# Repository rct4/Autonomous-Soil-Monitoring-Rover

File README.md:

# Autonomous-Soil-Monitoring-Rover

The autonomous soil monitoring rover is a project that aims to assist commercial farmers and personal gardeners by introducing an automated solution to monitoring soil data.

## Software
Motion plan is currently a naive solution, polling each sensor for feedback. A FreeRTOS solution is currently being developed to schedule sensor data collection and motor output.

## PCB

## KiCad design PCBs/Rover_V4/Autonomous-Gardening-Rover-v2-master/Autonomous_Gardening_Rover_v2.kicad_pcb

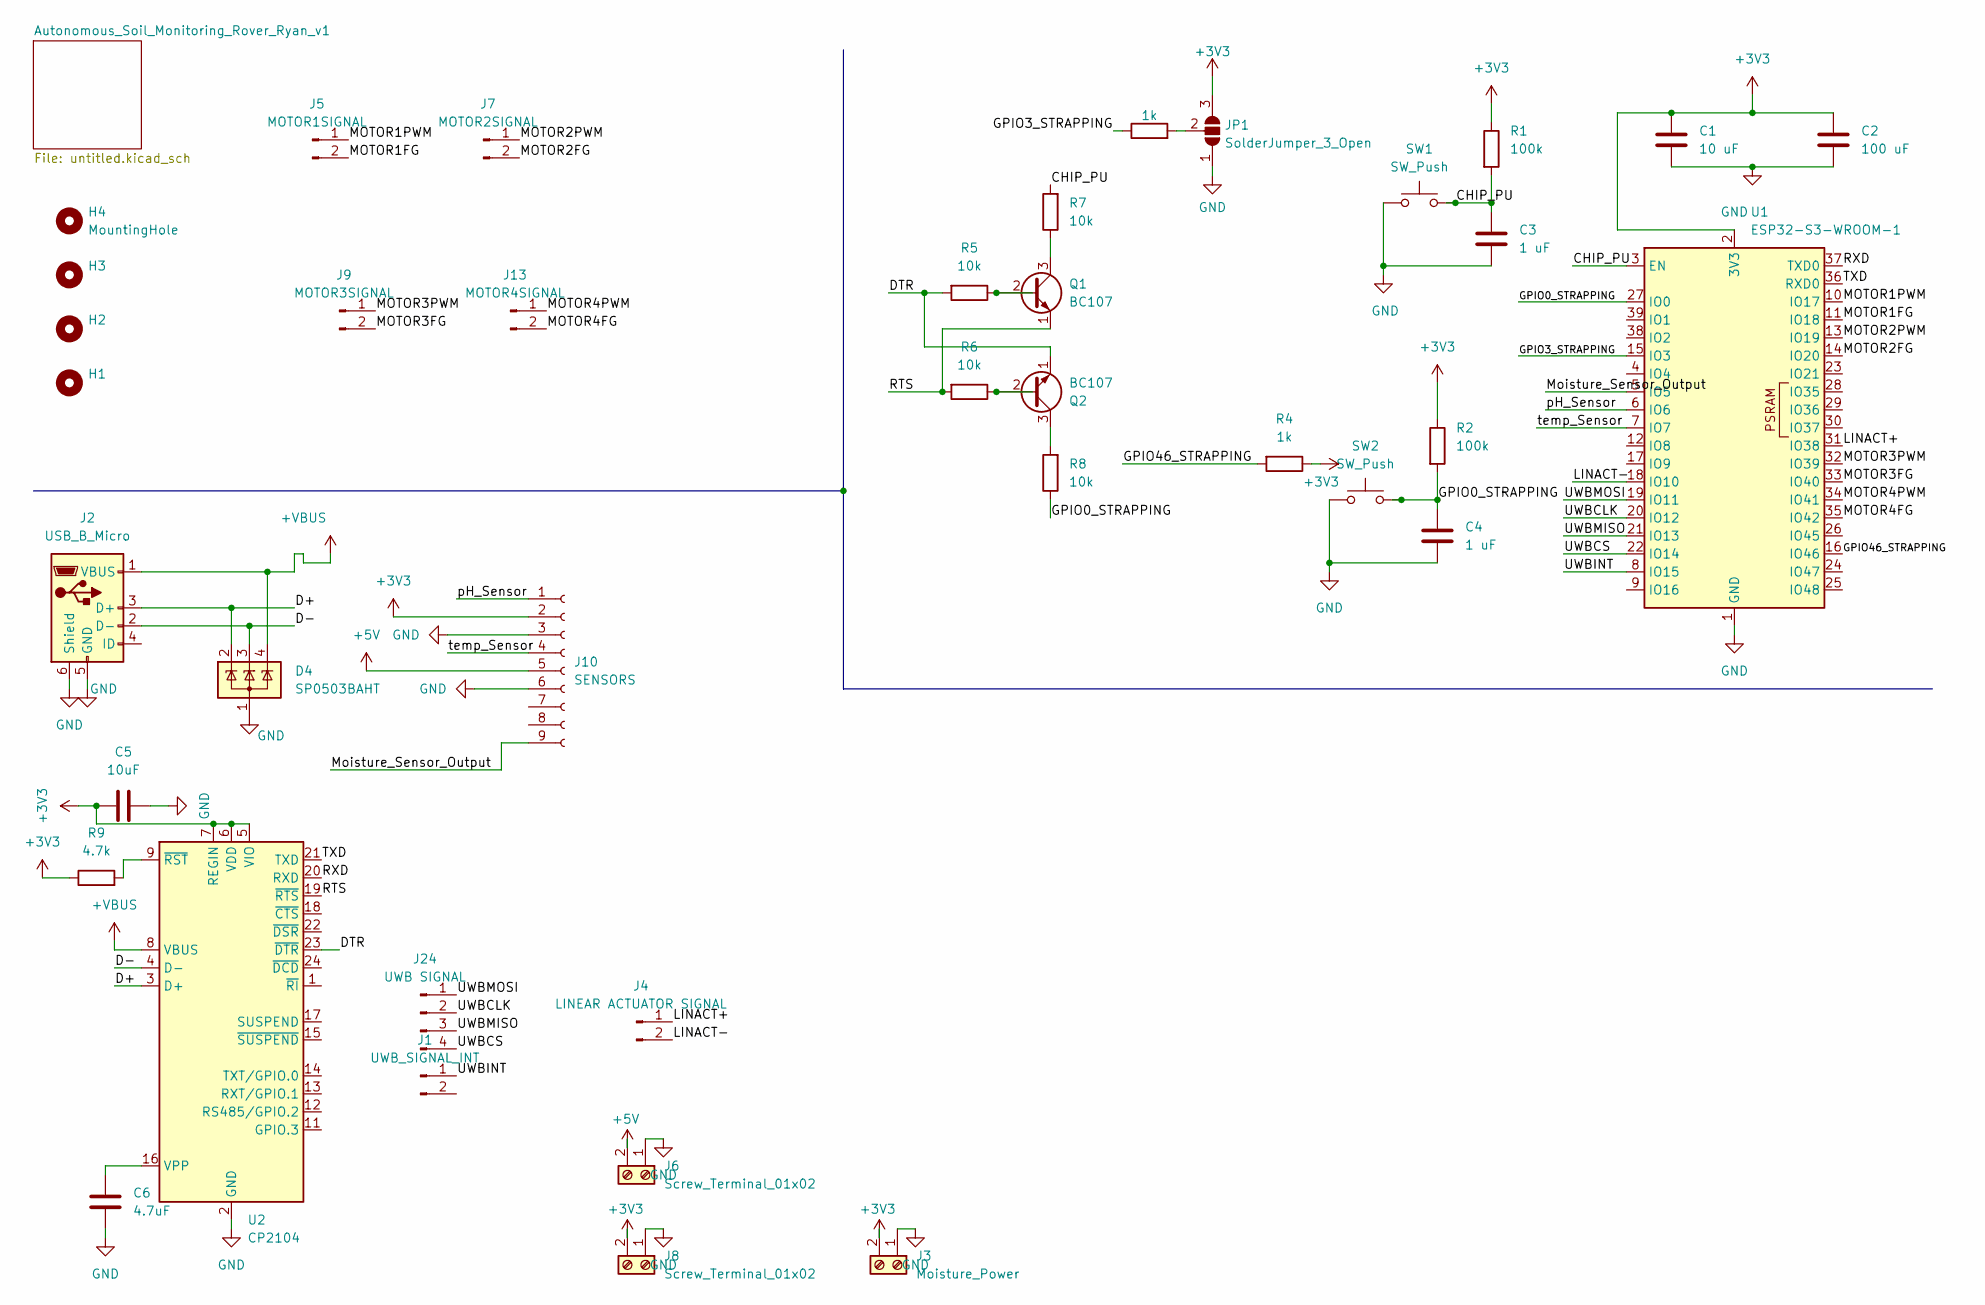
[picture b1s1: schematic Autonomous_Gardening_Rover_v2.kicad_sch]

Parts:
C1: 10 uF; C_0805_2012Metric_Pad1.18x1.45mm_HandSolder
C2: 100 uF; C_0805_2012Metric_Pad1.18x1.45mm_HandSolder
C3, C4: 1 uF; C_0805_2012Metric_Pad1.18x1.45mm_HandSolder
C5: 10uF; C_0805_2012Metric_Pad1.18x1.45mm_HandSolder
C6: 4.7uF; C_0805_2012Metric_Pad1.18x1.45mm_HandSolder
D4: SP0503BAHT; SOT-143
H1, H2, H3, H4: MountingHole; MountingHole_3.2mm_M3
J1: UWB_SIGNAL_INT; TerminalBlock_Phoenix_MKDS-1,5-2-5.08_1x02_P5.08mm_Horizont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
J2: USB_B_Micro; USB_Micro-B_Molex_47346-0001
J3: Moisture_Power; TerminalBlock_Phoenix_MKDS-1,5-2-5.08_1x02_P5.08mm_Horizont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
J4: LINEAR ACTUATOR SIGNAL; TerminalBlock_Phoenix_MKDS-1,5-2-5.08_1x02_P5.08mm_Horizont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
J5: MOTOR1SIGNAL; TerminalBlock_Phoenix_MKDS-1,5-2-5.08_1x02_P5.08mm_Horizont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
J6, J8: Screw_Terminal_01x02; TerminalBlock_Phoenix_MKDS-1,5-2-5.08_1x02_P5.08mm_Horizont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
J7: MOTOR2SIGNAL; TerminalBlock_Phoenix_MKDS-1,5-2-5.08_1x02_P5.08mm_Horizont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
J9: MOTOR3SIGNAL; TerminalBlock_Phoenix_MKDS-1,5-2-5.08_1x02_P5.08mm_Horizont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
J10: SENSORS; PinHeader_1x09_P2.54mm_Vertical
J13: MOTOR4SIGNAL; TerminalBlock_Phoenix_MKDS-1,5-2-5.08_1x02_P5.08mm_Horizont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
J24: UWB SIGNAL; TerminalBlock_Phoenix_MKDS-1,5-4-5.08_1x04_P5.08mm_Horizont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
JP1: SolderJumper_3_Open; SolderJumper-3_P2.0mm_Open_TrianglePad1.0x1.5mm
Q1, Q2: BC107; TO-18-3
R1, R2: 100k; R_0805_2012Metric_Pad1.20x1.40mm_HandSolder
R3: 1k; R_0805_2012Metric
R4: 1k; R_0805_2012Metric_Pad1.20x1.40mm_HandSolder
R5, R6, R7, R8: 10k; R_0805_2012Metric_Pad1.20x1.40mm_HandSolder
R9: 4.7k; R_0805_2012Metric_Pad1.20x1.40mm_HandSolder
SW1, SW2: SW_Push; SW_PUSH_6mm_H5mm
U1: ESP32-S3-WROOM-1; ESP32-S3-WROOM-1_EXP
U2: CP2104; QFN-24-1EP_4x4mm_P0.5mm_EP2.6x2.6mm

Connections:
+3V3: C1.1, C2.1, C5.1, J3.2, J8.2, J10.2, JP1.3 (B), R1.1, R2.1, R4.1, R9.1, U1.2 (3V3), U2.5 (VIO), U2.6 (VDD), U2.7 (REGIN)
+5V: J6.2, J10.5
+VBUS: D4.4 (K), J2.1 (VBUS), U2.8 (VBUS)
/CHIP_PU: C3.1, R1.2, R7.2, SW1.2, U1.3 (EN)
/D+: D4.2 (K), J2.3 (D+), U2.3 (D+)
/D-: D4.3 (K), J2.2 (D-), U2.4 (D-)
/DTR: Q2.1 (E), R5.2, U2.23 (~DTR)
/GPIO0_STRAPPING: C4.1, R2.2, R8.1, SW2.2, U1.27 (IO0)
/GPIO3_STRAPPING: R3.1, U1.15 (IO3)
/GPIO46_STRAPPING: R4.2, U1.16 (IO46)
/LINACT+: J4.1, U1.31 (IO38)
/LINACT-: J4.2, U1.18 (IO10)
/MOTOR1FG: J5.2, U1.11 (IO18)
/MOTOR1PWM: J5.1, U1.10 (IO17)
/MOTOR2FG: J7.2, U1.14 (IO20)
/MOTOR2PWM: J7.1, U1.13 (IO19)
/MOTOR3FG: J9.2, U1.33 (IO40)
/MOTOR3PWM: J9.1, U1.32 (IO39)
/MOTOR4FG: J13.2, U1.35 (IO42)
/MOTOR4PWM: J13.1, U1.34 (IO41)
/Moisture_Sensor_Output: J10.9, U1.5 (IO5)
/RTS: Q1.1 (E), R6.2, U2.19 (~RTS)
/RXD: U1.37 (TXD0), U2.20 (RXD)
/TXD: U1.36 (RXD0), U2.21 (TXD)
/UWBCLK: J24.2, U1.20 (IO12)
/UWBCS: J24.4, U1.22 (IO14)
/UWBINT: J1.1, U1.8 (IO15)
/UWBMISO: J24.3, U1.21 (IO13)
/UWBMOSI: J24.1, U1.19 (IO11)
/pH_Sensor: J10.1, U1.6 (IO6)
/temp_Sensor: J10.4, U1.7 (IO7)
GND: C1.2, C2.2, C3.2, C4.2, C5.2, C6.2, D4.1 (A), J2.5 (GND), J2.6 (Shield), J3.1, J6.1, J8.1, J10.3, J10.6, JP1.1 (A), SW1.1, SW2.1, U1.1 (GND), U1.40 (GND), U1.41 (GND), U2.2 (GND), U2.25 (GND)
unnamed: JP1.2 (C), R3.2
unnamed: Q1.2 (B), R5.1
unnamed: Q1.3 (C), R7.1
unnamed: Q2.2 (B), R6.1
unnamed: Q2.3 (C), R8.2
unnamed: C6.1, U2.16 (VPP)
unnamed: R9.2, U2.9 (~RST)

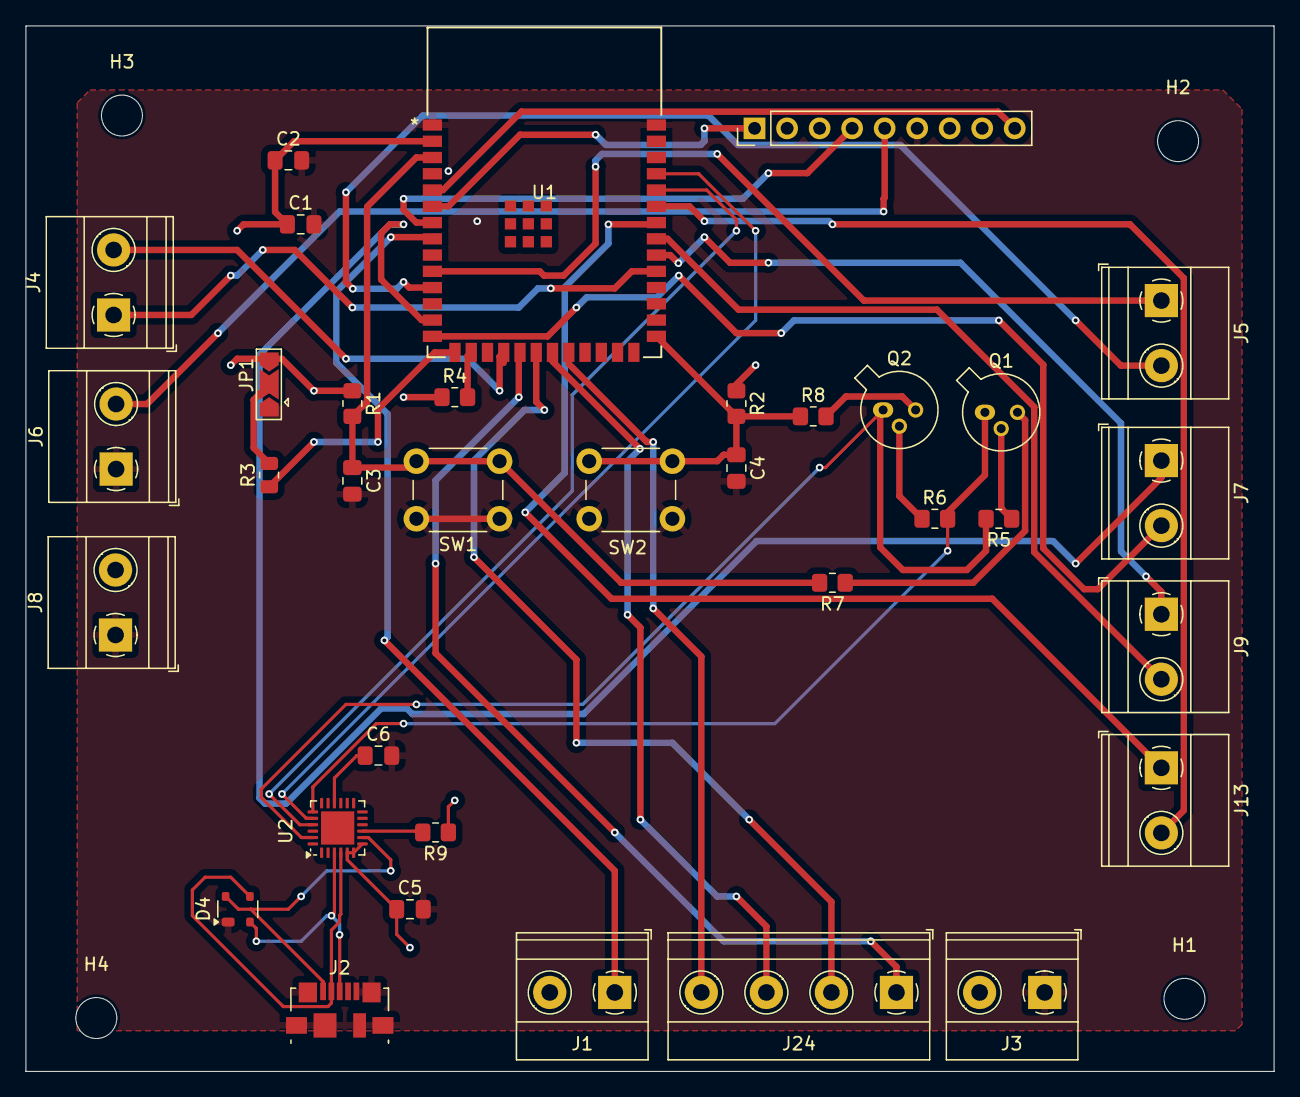
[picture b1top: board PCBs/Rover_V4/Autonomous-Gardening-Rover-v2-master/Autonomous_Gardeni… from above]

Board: 2 copper layers, 97.5 x 81.7 mm, 39 parts (0 on the bottom side), 39 nets.

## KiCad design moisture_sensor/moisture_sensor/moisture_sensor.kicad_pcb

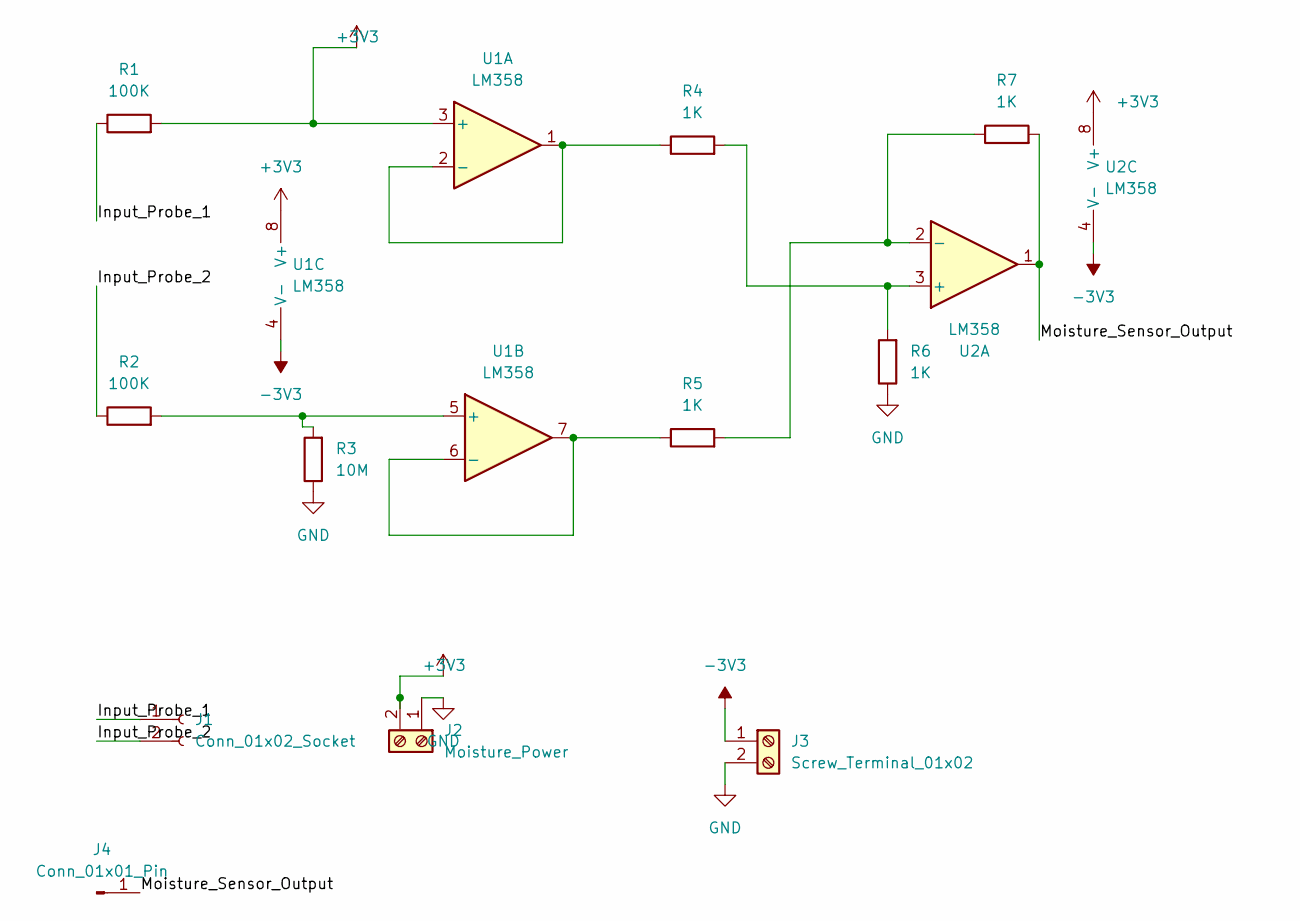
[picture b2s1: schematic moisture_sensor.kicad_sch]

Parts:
J1: Conn_01x02_Socket; PinHeader_1x02_P2.54mm_Vertical
J2: Moisture_Power; TerminalBlock_Phoenix_MKDS-1,5-2-5.08_1x02_P5.08mm_Horizont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
J3: Screw_Terminal_01x02; TerminalBlock_Phoenix_MKDS-1,5-2-5.08_1x02_P5.08mm_Horizont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
J4: Conn_01x01_Pin; PinHeader_1x01_P2.54mm_Vertical
R1, R2: 100K; R_0805_2012Metric_Pad1.20x1.40mm_HandSolder
R3: 10M; R_0805_2012Metric_Pad1.20x1.40mm_HandSolder
R4, R5, R6, R7: 1K; R_0805_2012Metric_Pad1.20x1.40mm_HandSolder
U1, U2: LM358; N08E

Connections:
+3V3: J2.2, R1.2, U1.3 (+), U1.8 (V+), U2.8 (V+)
-3V3: J3.1, U1.4 (V-), U2.4 (V-)
/Input_Probe_1: J1.1, R1.1
/Input_Probe_2: J1.2, R2.1
/Moisture_Sensor_Output: J4.1, R7.2, U2.1
GND: J2.1, J3.2, R3.1, R6.1
unnamed: R4.1, U1.1, U1.2 (-)
unnamed: R2.2, R3.2, U1.5 (+)
unnamed: R5.1, U1.6 (-), U1.7
unnamed: R4.2, R6.2, U2.3 (+)
unnamed: R5.2, R7.1, U2.2 (-)

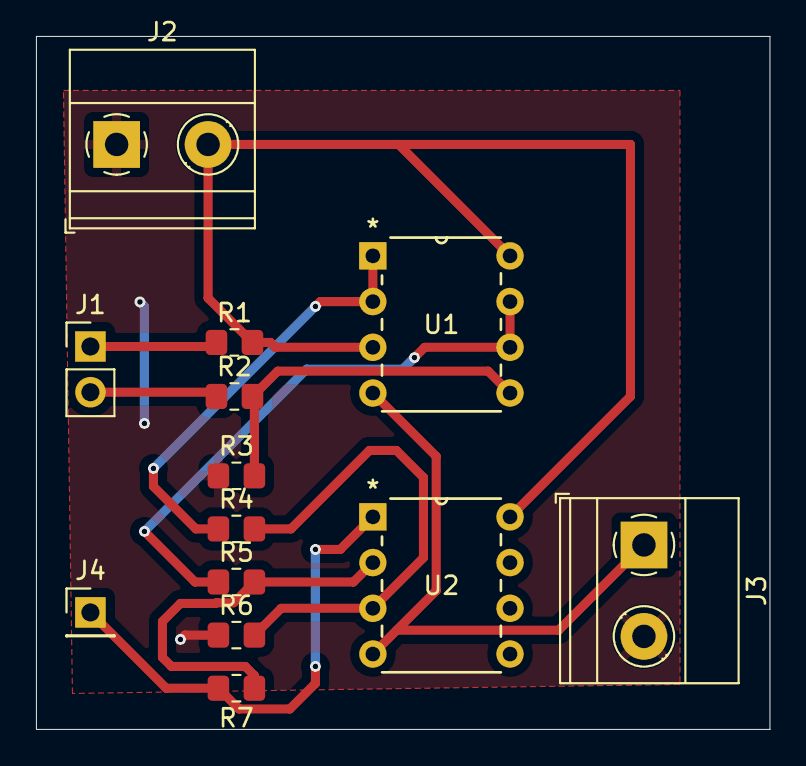
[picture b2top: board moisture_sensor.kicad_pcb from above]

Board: 2 copper layers, 40.8 x 38.5 mm, 13 parts (0 on the bottom side), 11 nets.

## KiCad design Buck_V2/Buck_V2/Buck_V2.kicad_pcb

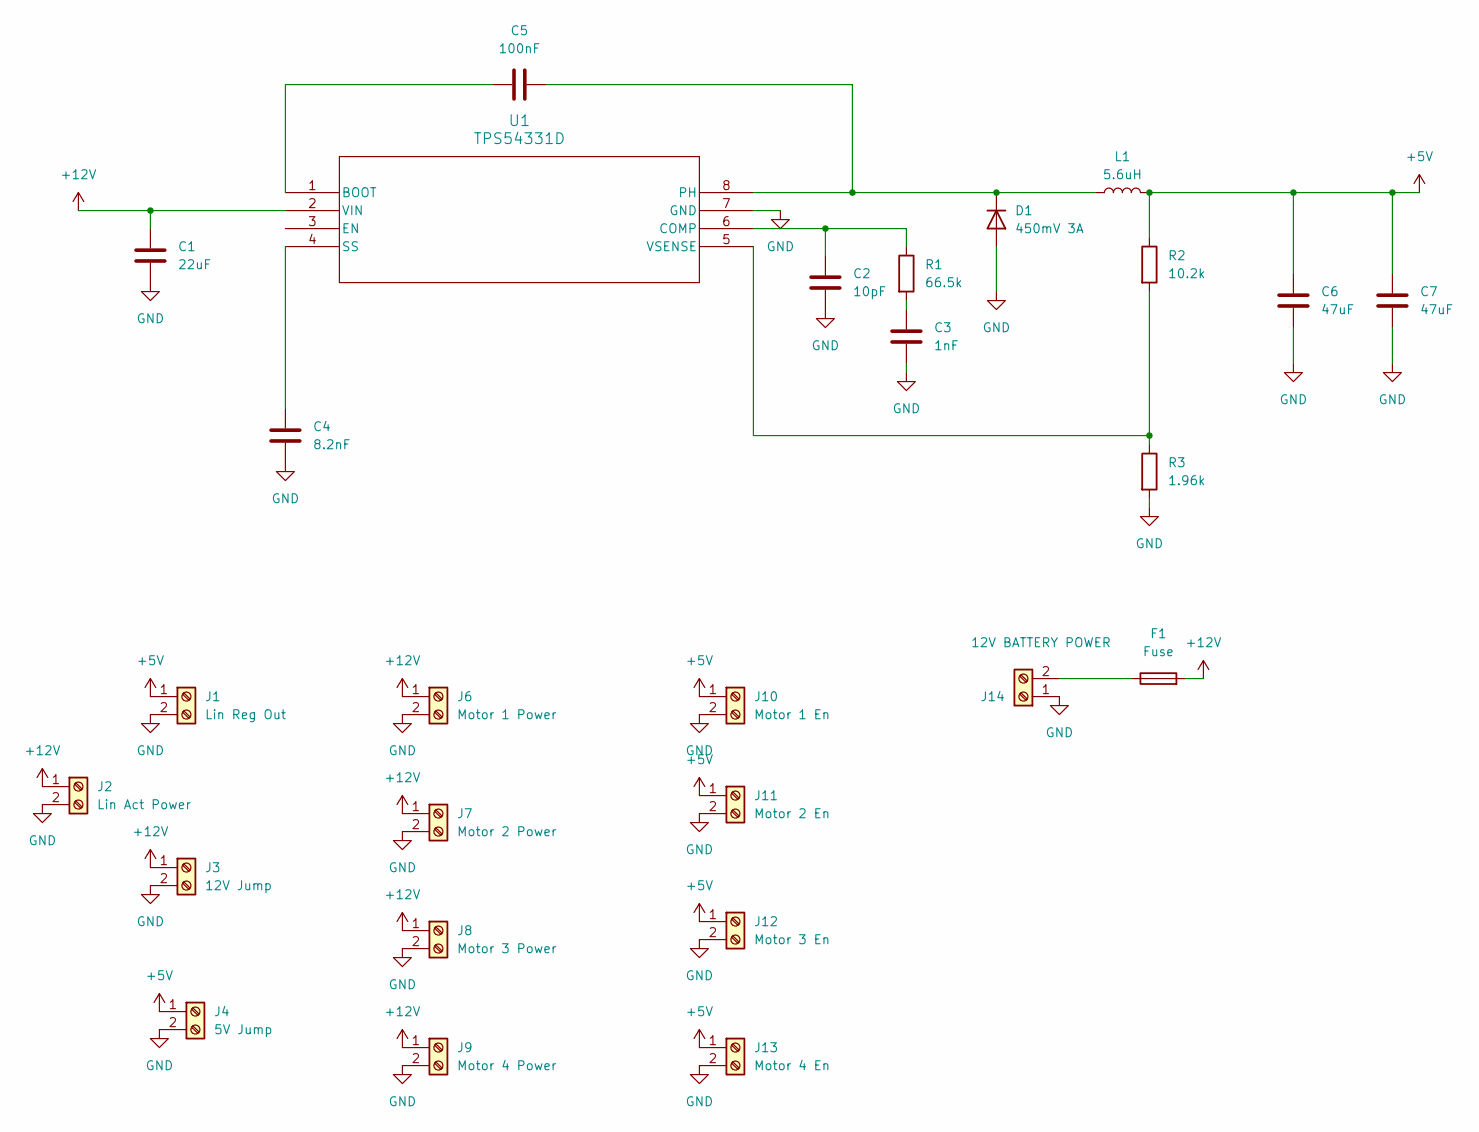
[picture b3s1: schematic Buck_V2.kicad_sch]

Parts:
C1: 22uF; C_0805_2012Metric_Pad1.18x1.45mm_HandSolder
C2: 10pF; C_0805_2012Metric_Pad1.18x1.45mm_HandSolder
C3: 1nF; C_0805_2012Metric_Pad1.18x1.45mm_HandSolder
C4: 8.2nF; C_1206_3216Metric_Pad1.33x1.80mm_HandSolder
C5: 100nF; C_0805_2012Metric_Pad1.18x1.45mm_HandSolder
C6, C7: 47uF; C_0805_2012Metric_Pad1.18x1.45mm_HandSolder
D1: 450mV 3A; DIODE_SODB340_2P92X4P6_DIO
F1: Fuse; Fuseholder_Littelfuse_Nano2_154x
J1: Lin Reg Out; TerminalBlock_Phoenix_MKDS-1,5-2-5.08_1x02_P5.08mm_Horizont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
J2: Lin Act Power; TerminalBlock_Phoenix_MKDS-1,5-2-5.08_1x02_P5.08mm_Horizont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
J3: 12V Jump; TerminalBlock_Phoenix_MKDS-1,5-2-5.08_1x02_P5.08mm_Horizont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
J4: 5V Jump; TerminalBlock_Phoenix_MKDS-1,5-2-5.08_1x02_P5.08mm_Horizont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
J6: Motor 1 Power; TerminalBlock_Phoenix_MKDS-1,5-2-5.08_1x02_P5.08mm_Horizont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
J7: Motor 2 Power; TerminalBlock_Phoenix_MKDS-1,5-2-5.08_1x02_P5.08mm_Horizont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
J8: Motor 3 Power; TerminalBlock_Phoenix_MKDS-1,5-2-5.08_1x02_P5.08mm_Horizont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
J9: Motor 4 Power; TerminalBlock_Phoenix_MKDS-1,5-2-5.08_1x02_P5.08mm_Horizont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
J10: Motor 1 En; TerminalBlock_Phoenix_MKDS-1,5-2-5.08_1x02_P5.08mm_Horizont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
J11: Motor 2 En; TerminalBlock_Phoenix_MKDS-1,5-2-5.08_1x02_P5.08mm_Horizont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
J12: Motor 3 En; TerminalBlock_Phoenix_MKDS-1,5-2-5.08_1x02_P5.08mm_Horizont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
J13: Motor 4 En; TerminalBlock_Phoenix_MKDS-1,5-2-5.08_1x02_P5.08mm_Horizont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
J14: 12V BATTERY POWER; TerminalBlock_Phoenix_MKDS-1,5-2-5.08_1x02_P5.08mm_Horizont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
L1: 5.6uH; IND25X25CZ
R1: 66.5k; R_0805_2012Metric_Pad1.20x1.40mm_HandSolder
R2: 10.2k; R_0805_2012Metric_Pad1.20x1.40mm_HandSolder
R3: 1.96k; R_0805_2012Metric_Pad1.20x1.40mm_HandSolder
U1: TPS54331D; D8

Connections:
+5V: C6.1, C7.1, J1.1, J4.1, J10.1, J11.1, J12.1, J13.1, L1.2, R2.1
+12V: C1.1, F1.2, J2.1, J3.1, J6.1, J7.1, J8.1, J9.1, U1.2 (VIN)
GND: C1.2, C2.2, C3.2, C4.2, C6.2, C7.2, D1.2 (A), J1.2, J2.2, J3.2, J4.2, J6.2, J7.2, J8.2, J9.2, J10.2, J11.2, J12.2, J13.2, J14.1, R3.2, U1.7 (GND)
unnamed: C3.1, R1.2
unnamed: C5.2, D1.1 (K), L1.1, U1.8 (PH)
unnamed: F1.1, J14.2
unnamed: C5.1, U1.1 (BOOT)
unnamed: C2.1, R1.1, U1.6 (COMP)
unnamed: C4.1, U1.4 (SS)
unnamed: R2.2, R3.1, U1.5 (VSENSE)

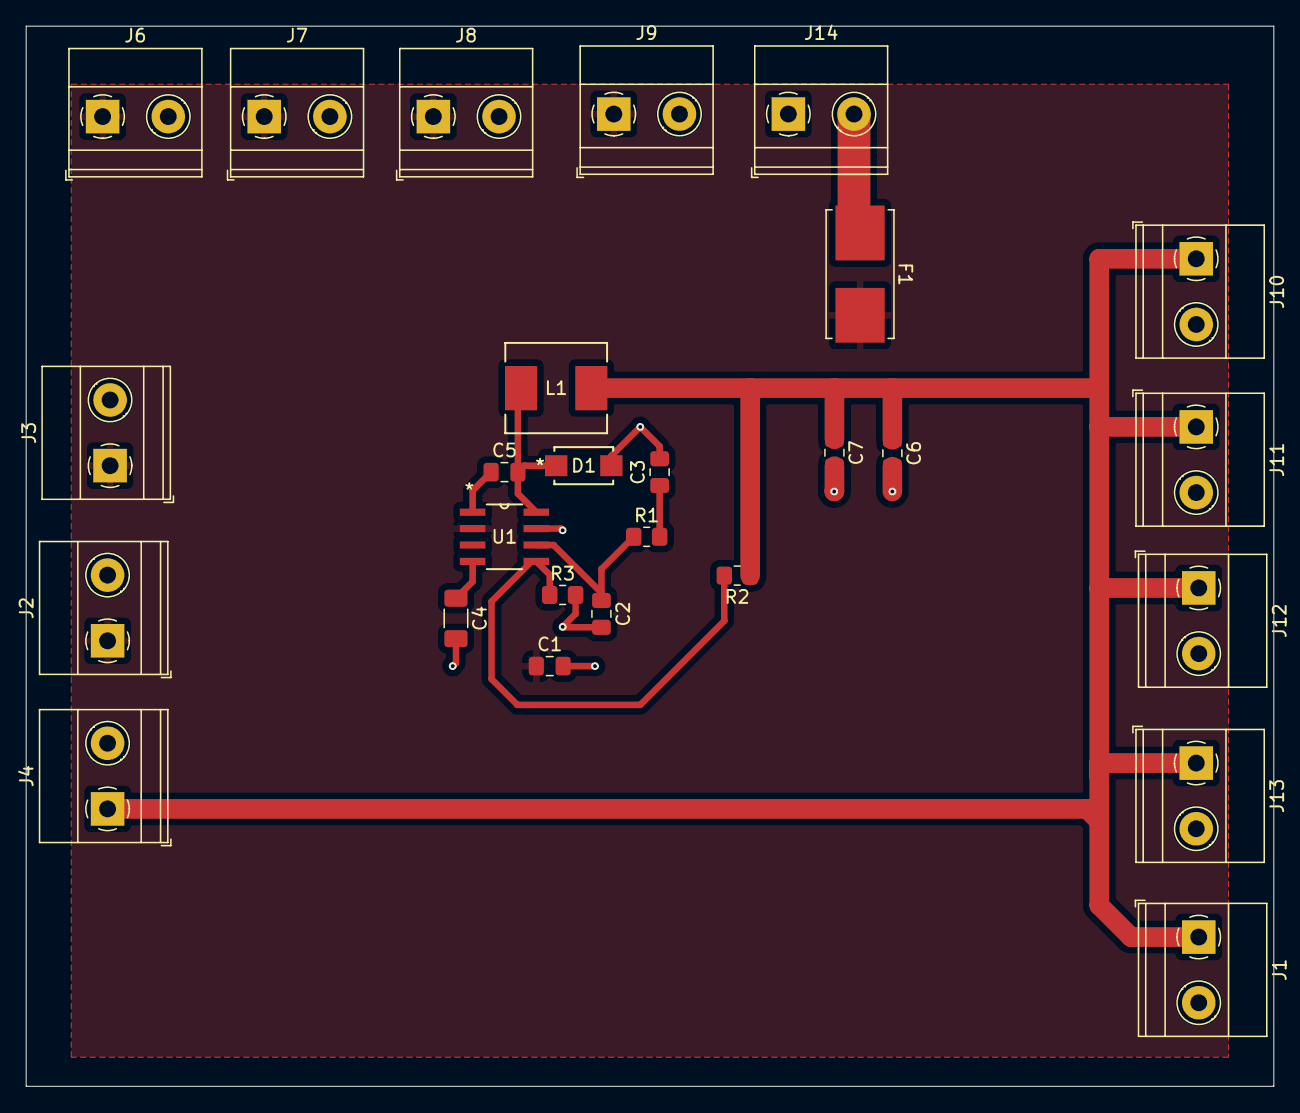
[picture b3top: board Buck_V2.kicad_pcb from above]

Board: 2 copper layers, 96.5 x 82.0 mm, 27 parts (0 on the bottom side), 10 nets.

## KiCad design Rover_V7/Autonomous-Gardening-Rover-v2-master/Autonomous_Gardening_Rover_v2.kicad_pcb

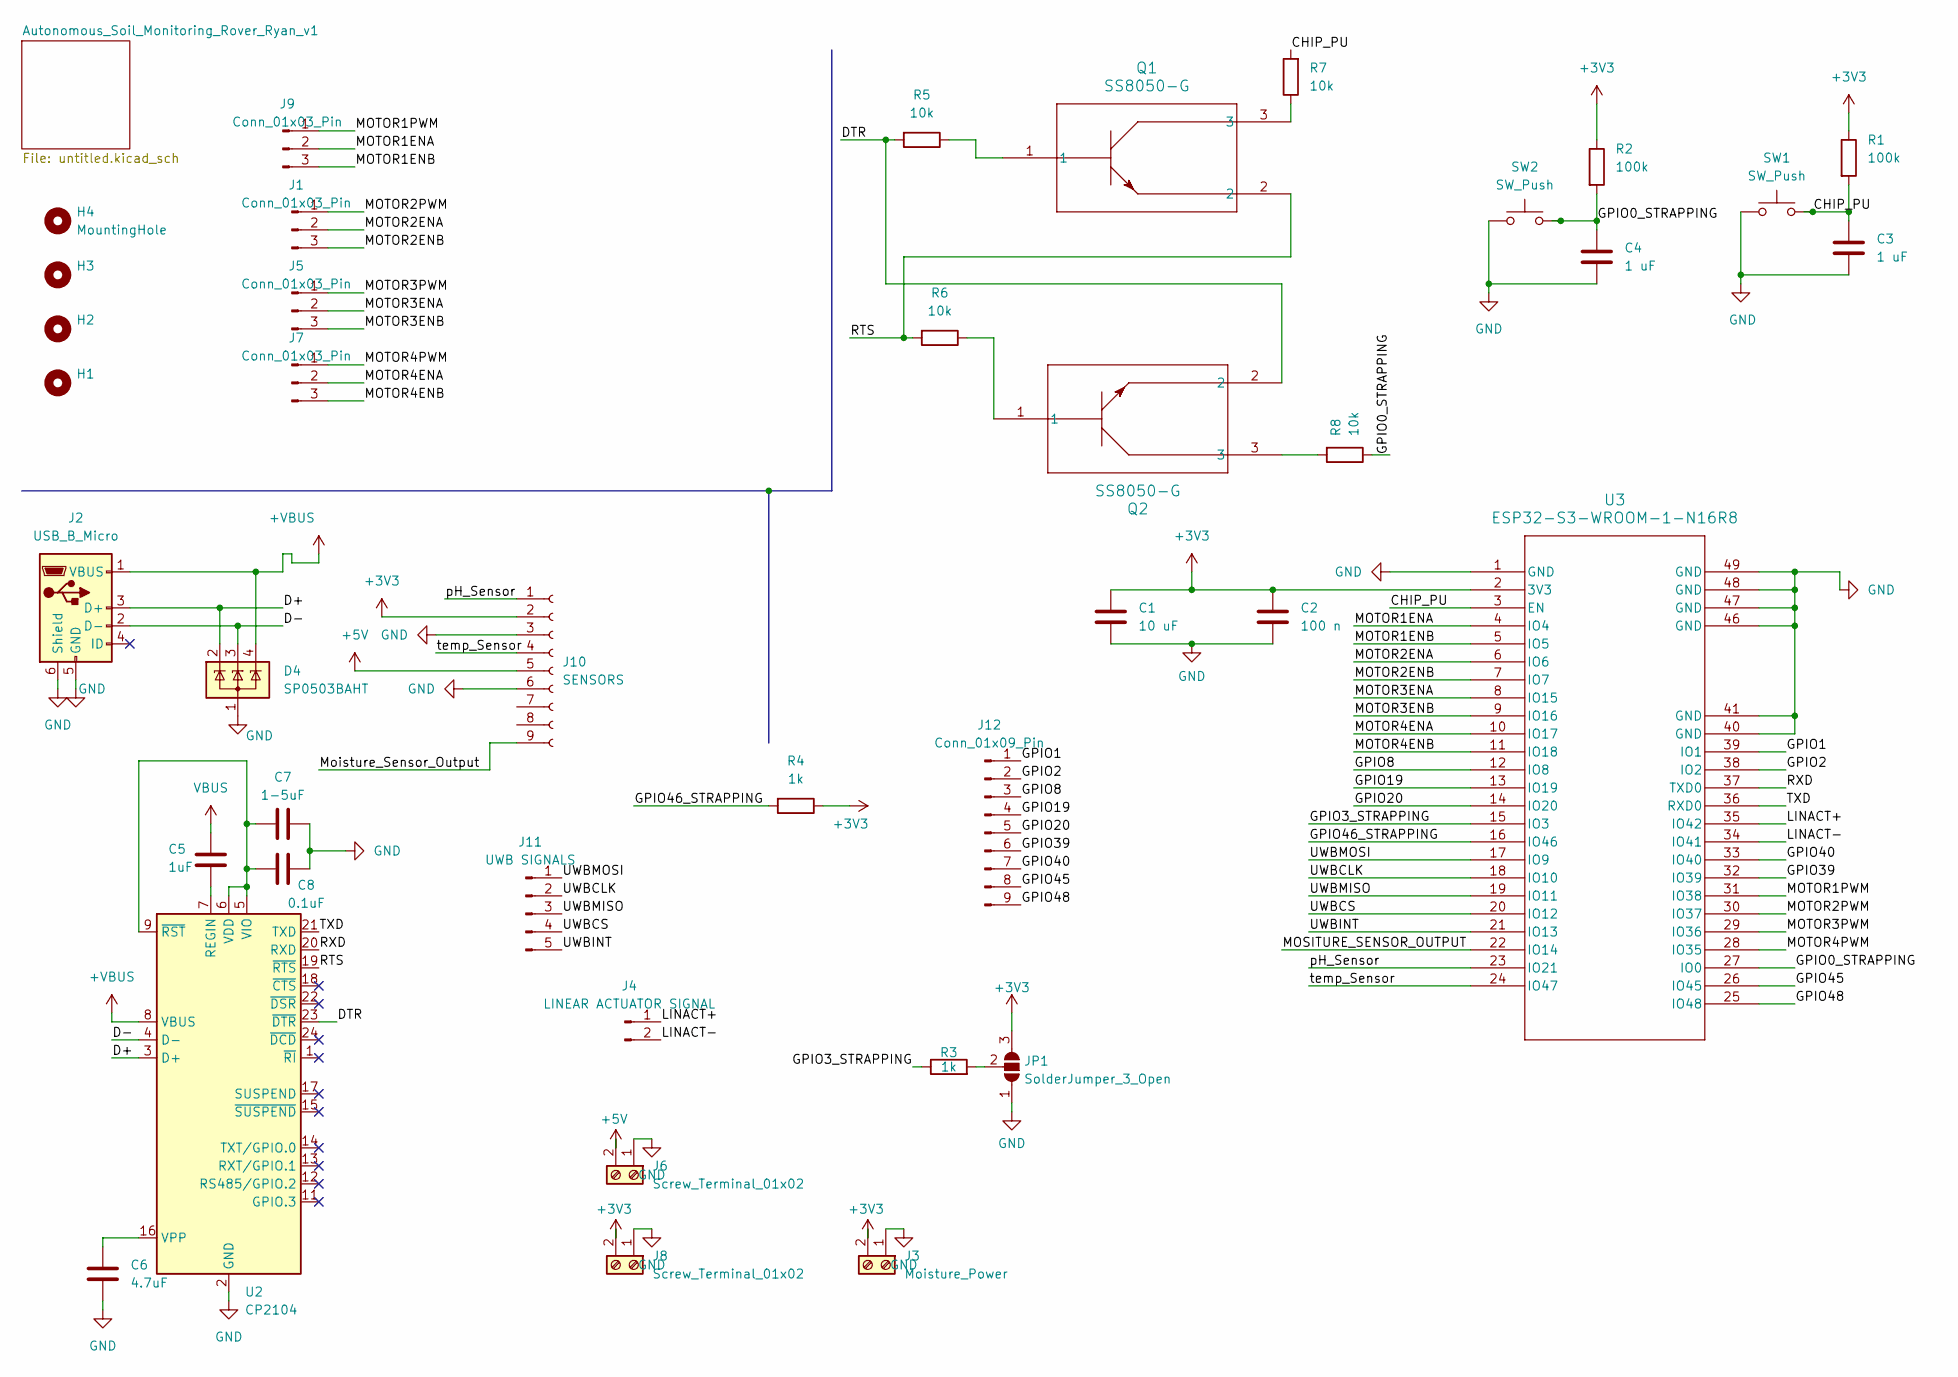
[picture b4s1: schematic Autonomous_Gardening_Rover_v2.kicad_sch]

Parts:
C1: 10 uF; C_0805_2012Metric_Pad1.18x1.45mm_HandSolder
C2: 100 n; C_0805_2012Metric_Pad1.18x1.45mm_HandSolder
C3, C4: 1 uF; C_0805_2012Metric_Pad1.18x1.45mm_HandSolder
C5: 1uF; C_0805_2012Metric_Pad1.18x1.45mm_HandSolder
C6: 4.7uF; C_0805_2012Metric_Pad1.18x1.45mm_HandSolder
C7: 1-5uF; C_0805_2012Metric_Pad1.18x1.45mm_HandSolder
C8: 0.1uF; C_0805_2012Metric_Pad1.18x1.45mm_HandSolder
D4: SP0503BAHT; SOT-143
H1, H2, H3, H4: MountingHole; MountingHole_3.2mm_M3
J1, J5, J7, J9: Conn_01x03_Pin; PinHeader_1x03_P2.54mm_Vertical
J2: USB_B_Micro; USB_Micro-B_Molex_47346-0001
J3: Moisture_Power; TerminalBlock_Phoenix_MKDS-1,5-2-5.08_1x02_P5.08mm_Horizont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
J4: LINEAR ACTUATOR SIGNAL; TerminalBlock_Phoenix_MKDS-1,5-2-5.08_1x02_P5.08mm_Horizont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
J6, J8: Screw_Terminal_01x02; TerminalBlock_Phoenix_MKDS-1,5-2-5.08_1x02_P5.08mm_Horizont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
J10: SENSORS; PinHeader_1x09_P2.54mm_Vertical
J11: UWB SIGNALS; PinHeader_1x05_P2.54mm_Vertical
J12: Conn_01x09_Pin; PinHeader_1x09_P2.54mm_Vertical
JP1: SolderJumper_3_Open; SolderJumper-3_P2.0mm_Open_TrianglePad1.0x1.5mm
Q1, Q2: SS8050-G; TRAN_SS8050-G_CIP
R1, R2: 100k; R_0805_2012Metric_Pad1.20x1.40mm_HandSolder
R3: 1k; R_0805_2012Metric
R4: 1k; R_0805_2012Metric_Pad1.20x1.40mm_HandSolder
R5, R6, R7, R8: 10k; R_0805_2012Metric_Pad1.20x1.40mm_HandSolder
SW1, SW2: SW_Push; SW_PUSH_6mm_H5mm
U2: CP2104; QFN-24-1EP_4x4mm_P0.5mm_EP2.6x2.6mm
U3: ESP32-S3-WROOM-1-N16R8; ESP32-S3-WROOM-1_EXP

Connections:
+3V3: C1.1, C2.1, J3.2, J8.2, J10.2, JP1.3 (B), R1.1, R2.1, R4.1, U3.2 (3V3)
+5V: J6.2, J10.5
+VBUS: D4.4 (K), J2.1 (VBUS), U2.8 (VBUS)
/CHIP_PU: C3.1, R1.2, R7.2, SW1.2, U3.3 (EN)
/D+: D4.2 (K), J2.3 (D+), U2.3 (D+)
/D-: D4.3 (K), J2.2 (D-), U2.4 (D-)
/DTR: Q2.2, R5.2, U2.23 (~DTR)
/GPIO0_STRAPPING: C4.1, R2.2, R8.1, SW2.2, U3.27 (IO0)
/GPIO1: J12.1, U3.39 (IO1)
/GPIO2: J12.2, U3.38 (IO2)
/GPIO3_STRAPPING: R3.1, U3.15 (IO3)
/GPIO8: J12.3, U3.12 (IO8)
/GPIO19: J12.4, U3.13 (IO19)
/GPIO20: J12.5, U3.14 (IO20)
/GPIO39: J12.6, U3.32 (IO39)
/GPIO40: J12.7, U3.33 (IO40)
/GPIO45: J12.8, U3.26 (IO45)
/GPIO46_STRAPPING: R4.2, U3.16 (IO46)
/GPIO48: J12.9, U3.25 (IO48)
/LINACT+: J4.1, U3.35 (IO42)
/LINACT-: J4.2, U3.34 (IO41)
/MOSITURE_SENSOR_OUTPUT: U3.22 (IO14)
/MOTOR1ENA: J9.2, U3.4 (IO4)
/MOTOR1ENB: J9.3, U3.5 (IO5)
/MOTOR1PWM: J9.1, U3.31 (IO38)
/MOTOR2ENA: J1.2, U3.6 (IO6)
/MOTOR2ENB: J1.3, U3.7 (IO7)
/MOTOR2PWM: J1.1, U3.30 (IO37)
/MOTOR3ENA: J5.2, U3.8 (IO15)
/MOTOR3ENB: J5.3, U3.9 (IO16)
/MOTOR3PWM: J5.1, U3.29 (IO36)
/MOTOR4ENA: J7.2, U3.10 (IO17)
/MOTOR4ENB: J7.3, U3.11 (IO18)
/MOTOR4PWM: J7.1, U3.28 (IO35)
/Moisture_Sensor_Output: J10.9
/RTS: Q1.2, R6.2, U2.19 (~RTS)
/RXD: U2.20 (RXD), U3.37 (TXD0)
/TXD: U2.21 (TXD), U3.36 (RXD0)
/UWBCLK: J11.2, U3.18 (IO10)
/UWBCS: J11.4, U3.20 (IO12)
/UWBINT: J11.5, U3.21 (IO13)
/UWBMISO: J11.3, U3.19 (IO11)
/UWBMOSI: J11.1, U3.17 (IO9)
/pH_Sensor: J10.1, U3.23 (IO21)
/temp_Sensor: J10.4, U3.24 (IO47)
GND: C1.2, C2.2, C3.2, C4.2, C6.2, C7.2, C8.2, D4.1 (A), J2.5 (GND), J2.6 (Shield), J3.1, J6.1, J8.1, J10.3, J10.6, JP1.1 (A), SW1.1, SW2.1, U2.2 (GND), U2.25 (GND), U3.1 (GND), U3.40 (GND), U3.41 (GND), U3.46 (GND), U3.47 (GND), U3.48 (GND), U3.49 (GND)
unnamed: JP1.2 (C), R3.2
unnamed: Q1.1, R5.1
unnamed: Q1.3, R7.1
unnamed: Q2.1, R6.1
unnamed: Q2.3, R8.2
unnamed: C5.2, U2.7 (REGIN)
unnamed: C7.1, C8.1, U2.5 (VIO), U2.6 (VDD), U2.9 (~RST)
unnamed: C6.1, U2.16 (VPP)
VBUS: C5.1

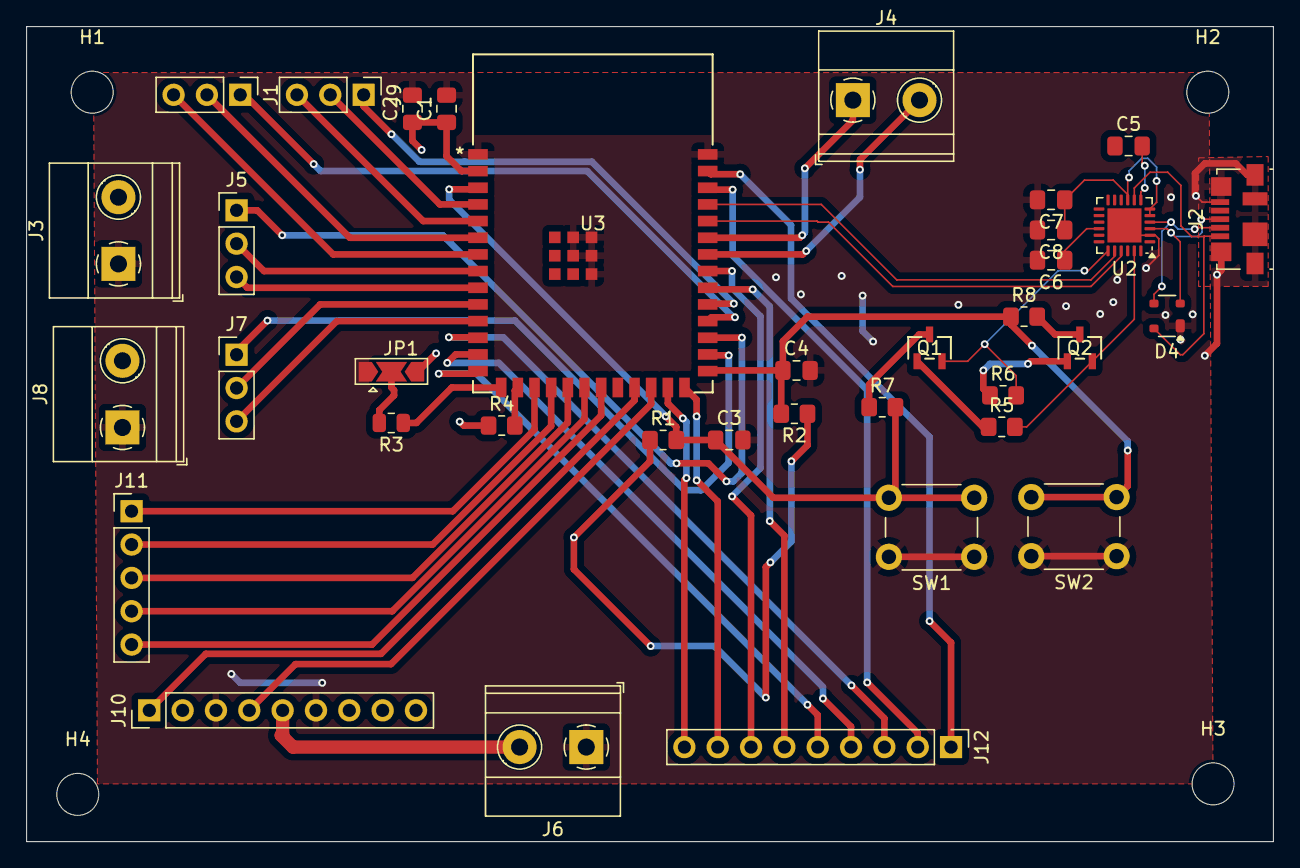
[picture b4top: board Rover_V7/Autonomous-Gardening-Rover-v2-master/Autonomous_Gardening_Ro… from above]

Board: 2 copper layers, 95.0 x 62.1 mm, 40 parts (0 on the bottom side), 52 nets.

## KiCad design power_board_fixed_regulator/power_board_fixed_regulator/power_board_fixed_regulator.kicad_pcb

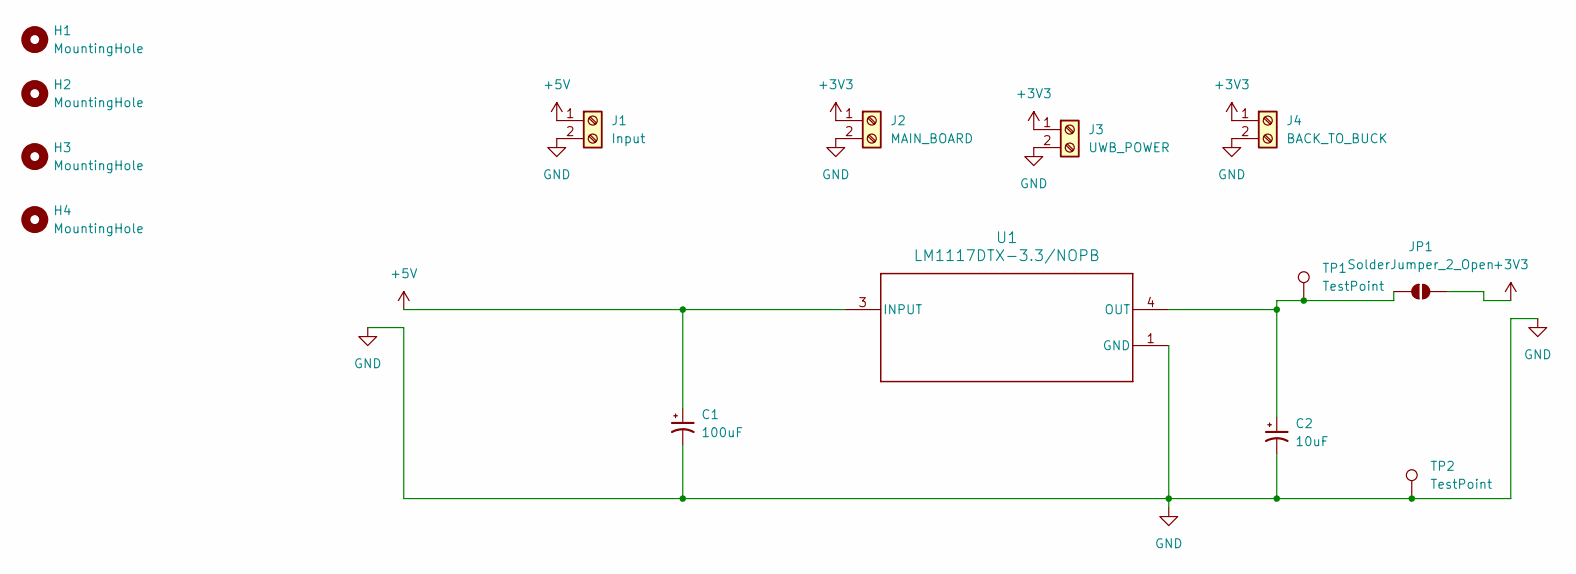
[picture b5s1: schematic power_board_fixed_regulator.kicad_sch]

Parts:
C1: 100uF; C_0805_2012Metric_Pad1.18x1.45mm_HandSolder
C2: 10uF; C_0805_2012Metric_Pad1.18x1.45mm_HandSolder
H1, H2, H3, H4: MountingHole; MountingHole_3.2mm_M3
J1: Input; TerminalBlock_Phoenix_MKDS-1,5-2-5.08_1x02_P5.08mm_Horizont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
J2: MAIN_BOARD; TerminalBlock_Phoenix_MKDS-1,5-2-5.08_1x02_P5.08mm_Horizont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
J3: UWB_POWER; TerminalBlock_Phoenix_MKDS-1,5-2-5.08_1x02_P5.08mm_Horizont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
J4: BACK_TO_BUCK; TerminalBlock_Phoenix_MKDS-1,5-2-5.08_1x02_P5.08mm_Horizont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
JP1: SolderJumper_2_Open; SolderJumper-2_P1.3mm_Open_RoundedPad1.0x1.5mm
TP1, TP2: TestPoint; TestPoint_Pad_2.5x2.5mm
U1: LM1117DTX-3.3/NOPB; NDP0003B

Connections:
+3V3: J2.1, J3.1, J4.1, JP1.2 (B)
+5V: C1.1, J1.1, U1.3 (INPUT)
GND: C1.2, C2.2, J1.2, J2.2, J3.2, J4.2, TP2.1, U1.1 (GND)
unnamed: C2.1, JP1.1 (A), TP1.1, U1.4 (OUT)

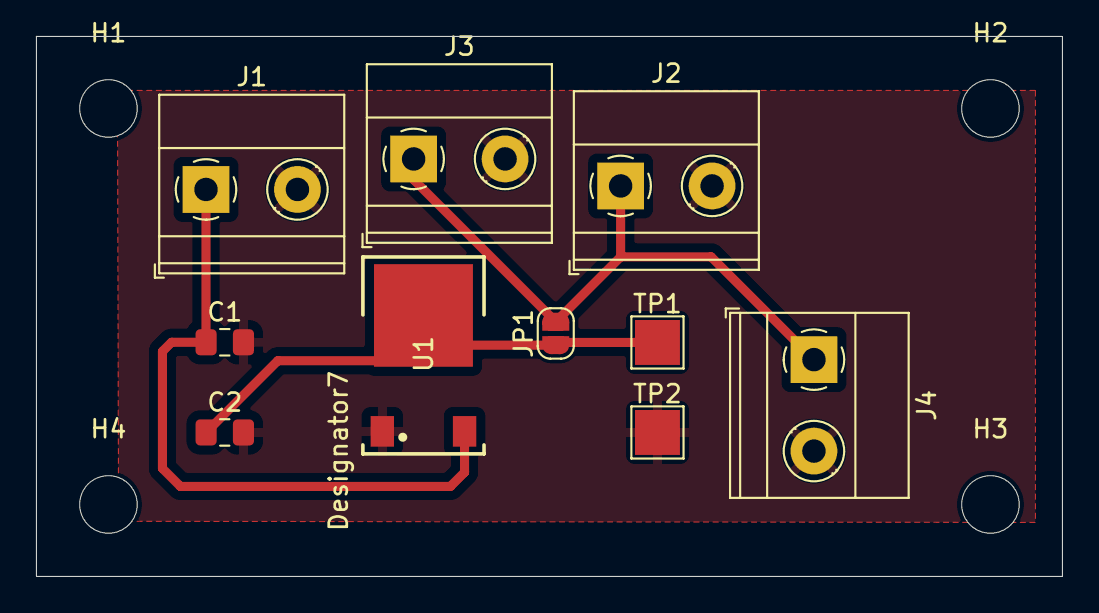
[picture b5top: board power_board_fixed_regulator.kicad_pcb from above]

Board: 2 copper layers, 57.0 x 30.0 mm, 14 parts (0 on the bottom side), 4 nets.
